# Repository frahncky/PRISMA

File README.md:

<div align="center">

### Plataforma de Registro, Instrumentação, Sinais, Medição e Análise

Analisador de energia trifásico em português: tensões, correntes, potências, FP, energia, demanda,<br>
formas de onda, fasores e harmônicas, ligado por serial à placa **DEMOEM / ColdFire MCF51EM256**.

**[Começar](#-começar-em-1-minuto)** ·
**[Recursos](#-recursos)** ·
**[Hardware](#-hardware-e-bancada)** ·
**[PCB AFE-LV](#-interface-de-seis-canais-afe-lv-a0)** ·
**[Estado](#-estado-do-projeto)** ·
**[Documentação](#-documentação)**

<br>

<sub>Captura real do aplicativo em modo demonstração · sinais sintéticos</sub>

</div>

<br>

> [!NOTE]
> **Protótipo v0.2.0.** Abre em modo demonstração e funciona sem placa. A DEMOEM já foi gravada e lida em bancada (CodeWarrior + PEmicro, telemetria via CH340). As leituras de ADC ainda são contagens brutas: a calibração metrológica está pendente. A primeira **interface de seis canais em KiCad (AFE-LV A0)** está disponível na [proposta de alteração #2](https://github.com/frahncky/PRISMA/pull/2), ainda sem liberação para fabricação.

## ⚡ Começar em 1 minuto

```powershell
git clone https://github.com/frahncky/PRISMA.git
cd PRISMA
py -m venv .venv
.\.venv\Scripts\python.exe -m pip install -e ".[dev]"
.\.venv\Scripts\python.exe -m prisma
```

Requer **Windows 11** e **Python 3.11+**. O app abre direto em demonstração: 2400 amostras/s, três fases de 127 V RMS a 60 Hz e 2,5 % de 3ª harmônica na fase A.

Com a placa:

```powershell
.\.venv\Scripts\python.exe -m prisma --port COM4 --profile examples\profiles\demoem-ch340.json --connect
.\.venv\Scripts\python.exe -m prisma --last          # reusa a última porta, perfil e monitor
.\.venv\Scripts\python.exe -m prisma --ligacao mono   # experimento monofásico (bi, tri); também no seletor do topo
.\.venv\Scripts\python.exe -m prisma --painel --screen 2   # painel touch em tela cheia no 2º monitor (ou F10)
.\scripts\criar_atalho.ps1                             # atalho "PRISMA" na área de trabalho
```

Pela rede (Wi-Fi), sem cabo entre a placa e a tela: o app conecta no gateway ESP32-S3 (`prisma.local`) ou na ponte do PC, que serve a serial da DEMOEM em TCP. Na lista de portas, escolha **Gateway na rede…**, ou passe o endereço:

```powershell
uv run python scripts\ponte_tcp.py COM3                 # neste PC: DEMOEM do CH340 na porta TCP 3333
uv run python scripts\ponte_tcp.py --demo               # sem placa: demonstração de 6 canais pela rede
.\.venv\Scripts\python.exe -m prisma --port 192.168.0.20:3333 --connect --painel   # em outro PC ou na tela
```

Numa tela dedicada (medidor), use o modo quiosque, que abre só o painel, conecta sozinho, reconecta e avisa quando os dados param: `python -m prisma --quiosque --port prisma.local` ([guia do quiosque](docs/quiosque.md), com partida automática no Windows e no Raspberry Pi).

O app reconecta sozinho se o Wi-Fi cair. Pela rede só passam os comandos de identificar, de rajada e de autocalibração; a atualização de firmware continua local ([protocolo](docs/protocolo.md#pela-rede-tcp)).

## ✨ Recursos

<table>
  <tr>
    <td width="33%" valign="top">
      <h3>📈 Medições</h3>
      Quadro de multimedidor por fase e trifásico (V, tensão de linha, I, P, Q, S, FP Indut./Capac.), osciloscópio Va/Vb/Vc, fasores com a fase A em 0°, harmônicas até h15 com THD, desequilíbrio e sequência de fases.
    </td>
    <td width="33%" valign="top">
      <h3>🔋 Energia e demanda</h3>
      Energia ativa importada/exportada e reativa, demanda de 15 min e máxima com horário, mínimos e máximos por fase. Calibração ganho/offset por canal.
    </td>
    <td width="33%" valign="top">
      <h3>📡 Aquisição serial</h3>
      JSON por linha via COM, perfis por placa, plugins de protocolo (JSON/CSV) e diagnóstico USB/serial do Windows.
    </td>
  </tr>
  <tr>
    <td valign="top">
      <h3>💾 Histórico</h3>
      Registro CSV contínuo e sessões SQLite com filtro temporal e exportação, sempre com origem e coeficientes de calibração.
    </td>
    <td valign="top">
      <h3>🔧 Build e gravação</h3>
      Projetos JSON com toolchain configurável, log, mapa de memória, hash do artefato e confirmação antes de gravar. Build CodeWarrior por linha de comando.
    </td>
    <td valign="top">
      <h3>📝 Editor e relatórios</h3>
      Editor de firmware C (<code>.c</code>/<code>.h</code>) e relatório HTML autossuficiente da análise, pronto para imprimir em PDF.
    </td>
  </tr>
</table>

<p align="center">
  <br>
  <sub><b>Painel touch</b> (<code>--painel</code> ou F10): Visão geral, Valores, Formas de onda, Fasores e harmônicas, Energia e demanda e Tendências, com alvos grandes para toque</sub>
</p>

<p align="center">
  <br>
  <sub><b>Tela de referência: 10,1" com 1280×800, IPS e toque capacitivo.</b> O painel cabe inteiro, sem rolagem (o layout pede no mínimo 1181×674). <a href="docs/images/painel-1280x800-todas.png">Ver as seis abas nesse tamanho</a></sub>
</p>

<table>
  <tr>
    <td align="center" width="50%"><br><sub>Análise, calibração e potências AC</sub></td>
    <td align="center" width="50%"><br><sub>Build com hash e mapa de memória</sub></td>
  </tr>
</table>

## 🧩 Como tudo se conecta

<p align="center">
  
  <br>
  <sub><b>Arquitetura conceitual.</b> A comunicação DEMOEM → PC por CH340 foi validada com três canais; o AFE-LV A0, a aquisição real de seis canais e a integração física com ESP32-S3 ainda requerem testes. Clique para ampliar.</sub>
</p>

<details>
<summary>Ver também o diagrama lógico em Mermaid</summary>

```mermaid
flowchart LR
    S["Sensores isolados<br/>tensão e corrente"] --> A["Condicionamento<br/>e filtros"]
    A --> B["DEMOEM<br/>ColdFire MCF51EM256"]
    B -->|"SCI3 · CH340 · 115200 8N1"| P["🖥️ PRISMA desktop"]
    B -.->|"UART"| G["Gateway ESP32-S3<br/>(protótipo)"]
    G -.->|"USB CDC"| P
    G -.->|"Wi-Fi · MQTT/TLS"| I["☁️ IoT"]
    G -.-> H["📱 Painel touch web"]
```

<sub>Linhas contínuas: telemetria de três canais validada em bancada. Tracejadas: integração física pendente.</sub>

</details>

## 🔌 Hardware e bancada

| Bancada validada | Configuração |
| --- | --- |
| **Placa** | DEMOEM com MCF51EM256 (ColdFire V1) |
| **Gravação** | CodeWarrior 6.3.2 + PEmicro Embedded Multilink (HI-WAVE) |
| **Telemetria** | `J6 PTC1/TX3 → CH340 RXD` + GND, J7/J8 sem jumper, perfil [`demoem-ch340.json`](examples/profiles/demoem-ch340.json) |
| **Formato** | Rajadas de 500 amostras × 3 canais a ~1995 Hz, uma linha JSON por bloco, 115200 8N1 (~1,2 blocos/s) |

```json
{"type":"sample","t":0.001,"va":110.2,"vb":-92.1,"vc":-18.3}
```

> [!WARNING]
> Nunca ligue tensão de rede direto ao ADC ou aos pinos do microcontrolador. Medições reais exigem transdutores **isolados** e condicionamento. Os valores exibidos são estimativas, sem calibração certificada.

Guias: [revisão da aquisição de seis canais](docs/revisao-aquisicao-seis-canais.md) · [ligações da placa](docs/ligacoes-hardware-demoem.md) · [modo quiosque](docs/quiosque.md) · [roteiro de bancada](docs/bancada-demoem.md) · [protocolo](docs/protocolo.md) · [bootloader/OTA](docs/bootloader.md) · [firmware ColdFire](firmware/README.md) · [gateway ESP32-S3](gateway/esp32s3/README.md)

## 🧰 Interface de seis canais — AFE-LV A0

A placa **DEMOEM/MCF51EM256** continua responsável pela aquisição. A revisão **AFE-LV A0** é uma **placa de interface de baixa tensão**, projetada para encaminhar seis sinais analógicos **já isolados e condicionados externamente** aos ADCs da DEMOEM. Os arquivos de projeto estão publicados na **[PR #2 — KiCad AFE-LV A0](https://github.com/frahncky/PRISMA/pull/2)** (branch de desenvolvimento; ainda não mesclada à `main`).

| Canal | ADC do ColdFire | Função prevista |
| --- | --- | --- |
| `Va`, `Vb`, `Vc` | `AD4/ADC3`, `AD5/ADC1`, `AD6/ADC2` | Três tensões previamente isoladas e condicionadas |
| `Ia`, `Ib`, `Ic` | `DADP0/ADC3`, `DADP1/ADC1`, `DADP2/ADC2` | Três correntes previamente isoladas e condicionadas; `DADM0/1/2` e `J29` dependem da topologia de entrada |

**Arquivos disponíveis na PR #2:**

- [Esquemático KiCad de seis canais](https://github.com/frahncky/PRISMA/blob/cad/afe-lv-a0-demoem-20261120/cad/afe-lv/prisma_afe_lv.kicad_sch) — 6 conectores de entrada, 6 saídas, resistores série, capacitores e pontos de teste.
- [Layout preliminar da PCB](https://github.com/frahncky/PRISMA/blob/cad/afe-lv-a0-demoem-20261120/cad/afe-lv/prisma_afe_lv.kicad_pcb) — duas camadas, trilhas iniciais e quatro furos de fixação.
- [Lista de componentes (BOM)](https://github.com/frahncky/PRISMA/blob/cad/afe-lv-a0-demoem-20261120/cad/afe-lv/BOM.csv) — valores de protótipo, sem fabricantes aprovados.
- [Guia de pinagem, limites e validação](https://github.com/frahncky/PRISMA/blob/cad/afe-lv-a0-demoem-20261120/cad/afe-lv/README.md) — conexão funcional prevista, verificação de `J29/J38` e ensaios seguros.

> [!CAUTION]
> **Ainda não é uma placa de medição para conexão à rede.** A AFE-LV A0 **não possui** transdutores de tensão/corrente, proteção e isolamento de rede, referência analógica/polarização, nem filtro anti-alias metrológico dimensionado. Seu RC de 1 kΩ/10 nF é apenas um filtro inicial de EMI. Os conectores da PCB **não reproduzem automaticamente a numeração física do J38**; identificar o lado do microcontrolador por esquema e continuidade com a placa desligada. Não conectar diretamente tensões de rede à PCB ou à DEMOEM e **não mandar fabricar** antes de concluir ERC/DRC e revisão elétrica.

**Para transformar a interface em um medidor real:** confirmar revisão física/pinagem da DEMOEM; selecionar modelos e datasheets dos três TVs e três TCs/sensores; projetar a proteção, a polarização e o filtro anti-alias; medir os seis canais com sinais seguros de baixa tensão; calibrar ganho, offset e fase; e validar erro, sincronismo e segurança. O [plano de aquisição e testes](docs/revisao-aquisicao-seis-canais.md) detalha esses critérios.

## 🗺️ Estado do projeto

| Entrega | Estado |
| --- | --- |
| Interface, instrumentos e editor em demonstração | ✅ Pronto |
| Análise: frequência, janelas, harmônicas, potência, calibração | ✅ Pronto em software |
| Histórico CSV / SQLite e relatórios | ✅ Pronto |
| Aquisição em rajada AD4/AD5/AD6 na DEMOEM (CH340, 115200 8N1) | ✅ Validada em bancada: trifásico a 120°, sem perda de blocos |
| Aquisição física completa de seis canais Va/Vb/Vc/Ia/Ib/Ic | ⏳ Pendente de validação com sensores reais e calibração de fase |
| AFE-LV A0 em KiCad (interface SELV de seis canais) | 🧪 Esquemático, layout e BOM na [PR #2](https://github.com/frahncky/PRISMA/pull/2); ERC/DRC e hardware pendentes |
| Build e gravação ColdFire (CodeWarrior + HI-WAVE) | ✅ Automatizados: `scripts/gravar_demoem.ps1 -Build` |
| Firmware ColdFire: rajada com timer, trim do oscilador gravado | ✅ Validados · autocalibração do ADC desativada |
| Telemetria por um único USB (serial virtual PEmicro) | ⏳ Driver atual não cria porta COM |
| Depuração ColdFire pelo PRISMA (GDB) | ⏳ Sem GDB ColdFire V1 na instalação; depuração via HI-WAVE |
| Medição calibrada e homologação física | ⏳ Pendente |
| Gateway ESP32-S3: ponte USB, resumos v2, MQTT e atualização da DEMOEM por Wi-Fi | 🧪 Compila no PlatformIO; núcleo testado no PC; não gravado num ESP |
| Tela touch física e bateria | 🧪 Projeto documentado, sem teste físico |

Detalhes por fase no [roadmap](docs/roadmap.md) e no [histórico de versões](CHANGELOG.md).

<details>
<summary><b>💾 Registrar amostras em CSV e SQLite</b></summary>

<br>

Com o modo demo ativo ou a serial recebendo amostras, use **Aquisição → Iniciar registro CSV…**. O arquivo traz `t_s`, `va_V`, `vb_V`, `vc_V`, `ia_A`, `ib_A`, `ic_A` e `origem` (UTF-8, vírgula como separador, ponto decimal). O registro continua além da janela dos gráficos sem manter tudo em memória e é encerrado ao trocar de fonte, desconectar ou fechar o app.

Em **Dados e dispositivos → Iniciar histórico SQLite…**, as sessões ficam no mesmo banco; **Consultar histórico SQLite…** exporta uma sessão inteira ou filtrada por tempo para CSV.

</details>

<details>
<summary><b>📐 Análise e relatórios</b></summary>

<br>

Na aba **Análise**, escolha 50 Hz, 60 Hz ou automático (40–70 Hz), janela retangular/Hann e a referência dos fasores. Clique na ponta de um fasor para inspecioná-lo. As harmônicas exibidas ficam sempre abaixo de Nyquist, conforme o maior intervalo entre amostras.

Na demonstração, as correntes são de 5 A RMS com FP 0,9. Na serial, as potências exigem `ia`, `ib` e `ic` sincronizadas. Métodos e limites em [instrumentação](docs/instrumentacao.md).

</details>

<details>
<summary><b>🔧 Compilação, gravação e depuração</b></summary>

<br>

Abra um projeto JSON na aba **Build / depuração**. Exemplos:

- [`host-gcc.json`](examples/projects/host-gcc.json): compila o simulador C no computador.
- [`demoem-codewarrior.json`](examples/projects/demoem-codewarrior.json): compila o firmware da DEMOEM via `CmdIDE` sem abrir a IDE.

A gravação exige comando configurado e confirmação explícita. Na bancada, gravação e depuração da DEMOEM são feitas pelo HI-WAVE. Veja o [guia de toolchain](docs/toolchain.md).

</details>

<details>
<summary><b>🧱 Arquitetura e estrutura do repositório</b></summary>

<br>

A interface roda na thread principal do Qt e a leitura serial em uma `QThread` própria. O núcleo separa protocolo, buffer de amostras e cálculos.

| Camada | Tecnologia |
| --- | --- |
| Aplicativo | Python 3.11+, PySide6 |
| Gráficos | pyqtgraph |
| Processamento | NumPy |
| Comunicação | pyserial, JSON por linha |
| Qualidade | pytest, GitHub Actions |

```text
src/prisma/        app: ui/ (janela, instrumentos, editor) e core/ (protocolo, cálculos, serial)
firmware/          encoder C, simulador host e projeto CodeWarrior da DEMOEM
gateway/esp32s3/   gateway PlatformIO: ponte USB, painel web, MQTT e atualização da DEMOEM
examples/          telemetria, calibração, perfis e projetos de toolchain
docs/              guias, protocolo, roadmap e imagens
scripts/           diagnóstico de drivers no Windows
tests/             protocolo, cálculos, firmware host e interface Qt
```

Mais em [arquitetura](docs/arquitetura.md).

</details>

<details>
<summary><b>🛠️ Desenvolvimento e testes</b></summary>

<br>

```powershell
.\.venv\Scripts\python.exe -m pytest -q
```

Os testes cobrem protocolo, serial fragmentada, cálculos trifásicos, frequência, potência, calibração, Nyquist, SQLite, relatórios, interface Qt sem tela, firmware host compilado com GCC e o cliente GDB/MI com processos de teste. O [GitHub Actions](https://github.com/frahncky/PRISMA/actions/workflows/ci.yml) roda a suíte a cada push e pull request.

</details>

## 📚 Documentação

| | Guia | Conteúdo |
| :-: | --- | --- |
| 🏛️ | [Arquitetura](docs/arquitetura.md) | Camadas do app e integração com o MCF51EM256 |
| 📨 | [Protocolo serial](docs/protocolo.md) | Mensagens, unidades e limites da telemetria |
| ⬆️ | [Bootloader/OTA](docs/bootloader.md) | Atualização do firmware pela serial, mapa de memória e segurança |
| 📐 | [Instrumentação](docs/instrumentacao.md) | Frequência, harmônicas, potências, calibração |
| 🔧 | [Toolchain](docs/toolchain.md) | Projetos, compilação, gravação e depuração |
| 🧩 | [Perfis e plugins](docs/plugins.md) | Adaptadores JSON/CSV e API de protocolos |
| 🧪 | [Bancada DEMOEM](docs/bancada-demoem.md) | Jumpers, testes e critérios de aceitação |
| 🔌 | [Ligações da placa](docs/ligacoes-hardware-demoem.md) | Alimentação, sensores, UART, touch, bateria e IoT |
| 🧰 | [AFE-LV A0 — interface KiCad](https://github.com/frahncky/PRISMA/blob/cad/afe-lv-a0-demoem-20261120/cad/afe-lv/README.md) | Esquemático, layout, BOM e validação de seis canais em **PR #2 (rascunho)** |
| 📡 | [Gateway ESP32-S3](gateway/esp32s3/README.md) | PlatformIO, ponte USB, painel touch, MQTT/TLS e OTA da DEMOEM |
| 💾 | [Firmware](firmware/README.md) | Encoder C, simulador host e projeto CodeWarrior |
| 🗺️ | [Roadmap](docs/roadmap.md) | Fases e pendências físicas |

## 🔒 Licença

Nenhuma licença de uso ou redistribuição foi concedida. O projeto é proprietário.

<div align="center">

<br>

<sub>Programar · Medir · Analisar</sub>

</div>

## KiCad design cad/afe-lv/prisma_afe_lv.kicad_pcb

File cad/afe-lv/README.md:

# PRISMA AFE-LV A0 — primeira placa de interface 6 canais (KiCad)

**Estado: desenho preliminar não testado**. Os arquivos KiCad foram gerados programaticamente, com estrutura de expressões balanceada, **mas não passaram pelo ERC/DRC do KiCad (ferramenta indisponível neste ambiente)**. **Não encomendar, energizar com rede elétrica, nem associar a calibração a uma classe de exatidão antes das verificações abaixo.**

## Arquivos
- `prisma_afe_lv.kicad_sch`: 6 células IN → R1k → ADC, C10n à referência GND e ponto de teste.
- `prisma_afe_lv.kicad_pcb`: roteamento inicial em duas camadas, aproximadamente **124 × 120 mm** (contorno x=6..130, y=15..135), montagem 4 × M3.
- `BOM.csv`: lista de itens e alternativas a confirmar.

### ATENÇÃO — objetivo limitado deste protótipo

Este circuito **não** mede tensão/corrente de rede sozinho. Os seis sinais `IN_VA`, `IN_VB`, `IN_VC`, `IN_IA`, `IN_IB`, `IN_IC` devem vir de **sensores isolados E de um estágio de condicionamento externo** que garanta, em todas as condições (incluindo transientes e falhas), uma saída dentro dos limites absolutos do ADC do MCF51EM256 **com referência compatível**. O filtro R1k/C10n tem apenas função de EMI/ruído em alta frequência (fc ideal ≈ 15,9 kHz) e **NÃO é filtro anti-alias adequado para 1995,5 Sa/s**. Não existe aqui TV, TC, burden, isolador, op-amp, proteção completa, fonte nem conector de rede elétrica.

Usar `GND` desta PCB apenas como retorno dos **domínios SELV isolados comprovados**, nunca neutro, fase ou PE como substituto sem análise formal de segurança. A referência de todas as seis saídas deve ser compatível; se os sensores tiverem retornos separados que não possam ser unidos, **esta PCB não é adequada sem revisão**. Cabeamento e proteção externa precisam impedir sobretensão no ADC mesmo com a DEMOEM desligada.

## Pinout da interface de protótipo

Cada **entrada J1–J6** e **saída J7–J12** possui apenas 2 pinos:

| Canal | Entrada | Saída | Pino 1 | Pino 2 | Destino funcional da saída |
|---|---|---|---|---|---|
| Va | J1 | J7 | sinal | GND | AD4, ADC3 |
| Vb | J2 | J8 | sinal | GND | AD5, ADC1 |
| Vc | J3 | J9 | sinal | GND | AD6, ADC2 |
| Ia | J4 | J10 | sinal | GND | DADP0, ADC3; DADM0 ligado a GND por J29 **apenas se compatível com condicionamento** |
| Ib | J5 | J11 | sinal | GND | DADP1, ADC1; DADM1 idem |
| Ic | J6 | J12 | sinal | GND | DADP2, ADC2; DADM2 idem |

**J7–J12 não são footprint nem pinagem direta de J38.** São 6 conectores de 2 pinos para cabos/adaptador **a identificar por continuidade no J38/J1 físico, lado MCU**, com J38 desligando QE8. Não conectar um cabo 2×6 diretamente à DEMOEM por suposição. Pin 1 dos headers está marcado pelo pad retangular; ver orientação de PCB após abrir no KiCad.

### Decisões técnicas
1. Resistores 1k ±1% em série: limitam pequenas correntes transientes e constituem filtro RC com C10n. **Não garantem proteção a sobretensão**.
2. Capacitores 10nF C0G/NP0 0805, 50 V, ao GND: baixa deriva, mas a capacitância e impedância de origem devem ser validadas para a precisão pretendida.
3. Cabeçalhos 2,54 mm são apenas para **protótipo SELV**. Substituir por conectores polarizados/travados no produto final e fazer novo DRC.
4. Rastros F.Cu para sinal, B.Cu para retorno. O layout possui trilhas de GND conectando os canais; não inclui plano de GND nem guarda analógica. Medir ruído e acoplamento antes de declarar desempenho.
5. A interface não produz deslocamento a 1,65 V. Esse **offset deve ser fornecido e estabilizado pelo AFE externo**.

## Verificação obrigatória no KiCad antes de fabricar
- [ ] Abrir ambos arquivos no KiCad 8/9 e salvar novamente com a versão instalada.
- [ ] Executar ERC e DRC com a biblioteca de footprints instalada; resolver 100% dos **erros**, e analisar todos os avisos.
- [ ] Confirmar que o símbolo `PRISMA:Conn02` embutido e os 12 footprints de cabeçalho preservam a numeração 1=sinal, 2=GND.
- [ ] Conferir footprints R/C 0805 e disponibilidade exata das peças e padstacks.
- [ ] Conferir em inspeção visual e com DRC todos os cruzamentos de trilha, pads, furos e afastamentos.
- [ ] Conferir a geometria dos quatro furos M3 e a distância mínima das trilhas e das bordas.
- [ ] Confirmar continuidade elétrica ponta a ponta **após montagem, sem DEMOEM conectada**.
- [ ] Gerar Gerbers/BOM/arquivos de furação apenas depois dessas etapas.

## Ensaio sem rede
1. Identificar o lado do MCU em J38 e orientação de J29/J1 na placa real, com multímetro e esquema rev. C, **sem energizar**.
2. Testar esta interface isoladamente com fonte/gerador **SELV** de 0,3 a 3,0 V; verificar os seis canais em DC e senoidal e ausência de curtos/contato cruzado.
3. Conectar à DEMOEM somente após medir cada saída com multímetro/osciloscópio e comprovar níveis permitidos em VDD e em desligamento.
4. Conferir assinatura de cada canal na aquisição `0x3F`, `adc_timeout_mask`, sequência, CRC e offsets.
5. Medir ganho e defasagem entre canais e o efeito do RC; projetar posteriormente **filtro anti-alias de ordem apropriada** com base na banda/harmônicas pretendidas.
6. Repetir com os modelos de TVs/TCs escolhidos **após** projeto formal de isolamento e proteção do AFE externo.

## O que continua pendente (não fingir concluído)
- Fotografia/revisão física da DEMOEM; confirmação de cada pino de J38 por continuidade.
- Modelo/faixa/datasheet dos três TVs e dos três TCs, burden e isolação; fonte de alimentação e proteção.
- **AFE metrológico completo** com polarização/buffer/anti-alias e clamps dimensionados por datasheet, com ERC/DRC.
- Ensaios físicos de seis canais, calibração ganho/fase, precisão e atualização dos respectivos registros do PRISMA.
- Validar no hardware o ESP32-S3, a tela física, bateria/power-path, IoT, firmware/bootloader e documentação de segurança.

## Fontes
- [NXP DEMOEM User Manual](https://www.nxp.com/docs/en/user-guide/DEMOEMUM.pdf)
- [NXP DEMOEMSC rev. C](https://www.nxp.com/downloads/en/schematics/DEMOEMSC.pdf)
- [NXP MCF51EM256](https://www.nxp.com/products/MCF51EM)
- [Revisão de aquisição PRISMA](../../docs/revisao-aquisicao-seis-canais.md)

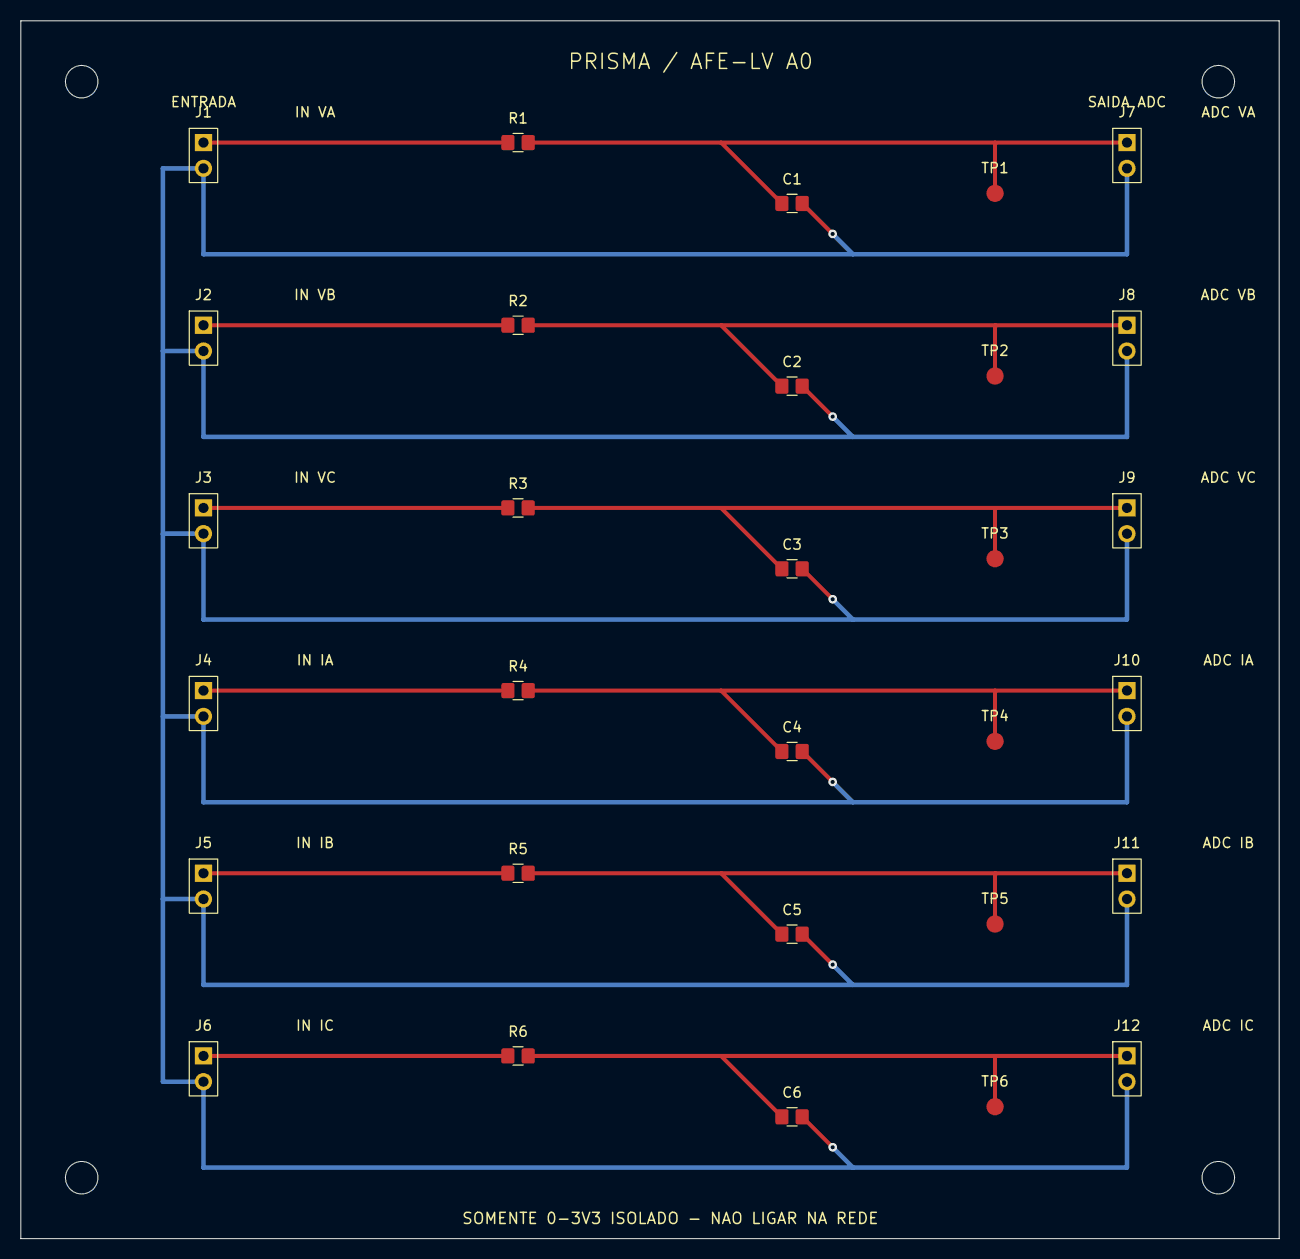
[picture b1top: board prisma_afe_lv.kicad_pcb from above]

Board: 2 copper layers, 124.0 x 120.0 mm, 34 parts (0 on the bottom side), 13 nets.

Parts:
C1, C2, C3, C4, C5, C6: 10n; C_0805_2012Metric
H1, H2, H3, H4: M3; MountingHole_3.2mm_M3
J1: IN_VA; PinHeader_1x02_P2.54mm_Vertical
J2: IN_VB; PinHeader_1x02_P2.54mm_Vertical
J3: IN_VC; PinHeader_1x02_P2.54mm_Vertical
J4: IN_IA; PinHeader_1x02_P2.54mm_Vertical
J5: IN_IB; PinHeader_1x02_P2.54mm_Vertical
J6: IN_IC; PinHeader_1x02_P2.54mm_Vertical
J7: ADC_VA; PinHeader_1x02_P2.54mm_Vertical
J8: ADC_VB; PinHeader_1x02_P2.54mm_Vertical
J9: ADC_VC; PinHeader_1x02_P2.54mm_Vertical
J10: ADC_IA; PinHeader_1x02_P2.54mm_Vertical
J11: ADC_IB; PinHeader_1x02_P2.54mm_Vertical
J12: ADC_IC; PinHeader_1x02_P2.54mm_Vertical
R1, R2, R3, R4, R5, R6: 1k; R_0805_2012Metric
TP1: ADC_VA; TestPoint_Pad_D1.5mm
TP2: ADC_VB; TestPoint_Pad_D1.5mm
TP3: ADC_VC; TestPoint_Pad_D1.5mm
TP4: ADC_IA; TestPoint_Pad_D1.5mm
TP5: ADC_IB; TestPoint_Pad_D1.5mm
TP6: ADC_IC; TestPoint_Pad_D1.5mm

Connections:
ADC_IA: C4.1, J10.1, R4.2, TP4.1
ADC_IB: C5.1, J11.1, R5.2, TP5.1
ADC_IC: C6.1, J12.1, R6.2, TP6.1
ADC_VA: C1.1, J7.1, R1.2, TP1.1
ADC_VB: C2.1, J8.1, R2.2, TP2.1
ADC_VC: C3.1, J9.1, R3.2, TP3.1
GND: C1.2, C2.2, C3.2, C4.2, C5.2, C6.2, J1.2, J2.2, J3.2, J4.2, J5.2, J6.2, J7.2, J8.2, J9.2, J10.2, J11.2, J12.2
IN_IA: J4.1, R4.1
IN_IB: J5.1, R5.1
IN_IC: J6.1, R6.1
IN_VA: J1.1, R1.1
IN_VB: J2.1, R2.1
IN_VC: J3.1, R3.1
